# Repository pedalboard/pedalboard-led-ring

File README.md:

# An addressable RGB LED ring around foot button

| Open Source Hardware | OSHWA Certification|
|---|---|
|  |  |

Features:

- Each of the 12 LEDs on the ring can get an individual color.
- The led rings can be cascaded and addressed via a single serial line.
- Connector options: SMD Sockets (2mm, 4 Pins)
- Optional solution to drive the LED ring directly from 3.3V data pin, however the 1st LED have a bit lower intensity.

See a [live demo](https://www.youtube.com/watch?v=p5gpGeihErE) where the LED ring is used to represent the LUVS loudness value of signal.

| Top View | Bottom View  |
| -------- | ------------ |
|  |   |
|  |  |

## Generated Hardware Documentation

Interactive [KiCanvas](https://kicanvas.org/?github=https%3A%2F%2Fgithub.com%2Fpedalboard%2Fpedalboard-led-ring%2Ftree%2Fmain) viewer.

Downloadable [Assets](https://pedalboard.github.io/pedalboard-led-ring/latest) are generated with [KiBot](https://github.com/INTI-CMNB/KiBot)

## Fabrication

* [Generated iBOM](https://pedalboard.github.io/pedalboard-led-ring/latest/Assembly/pedalboard-led-ring-ibom.html)
* [Digi-Key shared list](https://www.digikey.ch/de/mylists/list/I3LZUQ0FSV)
* [PCBWay manifacturing](https://www.pcbway.com/project/shareproject/FIXME.html)

## Additional mechanical components

* Foot switch actuator: [Data Sheet](https://www.cliffuk.co.uk/products/switches/FC7125.pdf) [3D Model](https://github.com/pedalboard/pedalboard-case/blob/main/generated/actuator.stl)
* Lens: [3D Model](https://github.com/pedalboard/pedalboard-case/blob/main/generated/led-ring-washer.stl) Potential [material](https://plastics-rubber.basf.com/global/de/performance_polymers/products/ultramid.html)

## Release

The release procedure is the same as for [pedalboard-hw](https://github.com/pedalboard/pedalboard-hw#release)

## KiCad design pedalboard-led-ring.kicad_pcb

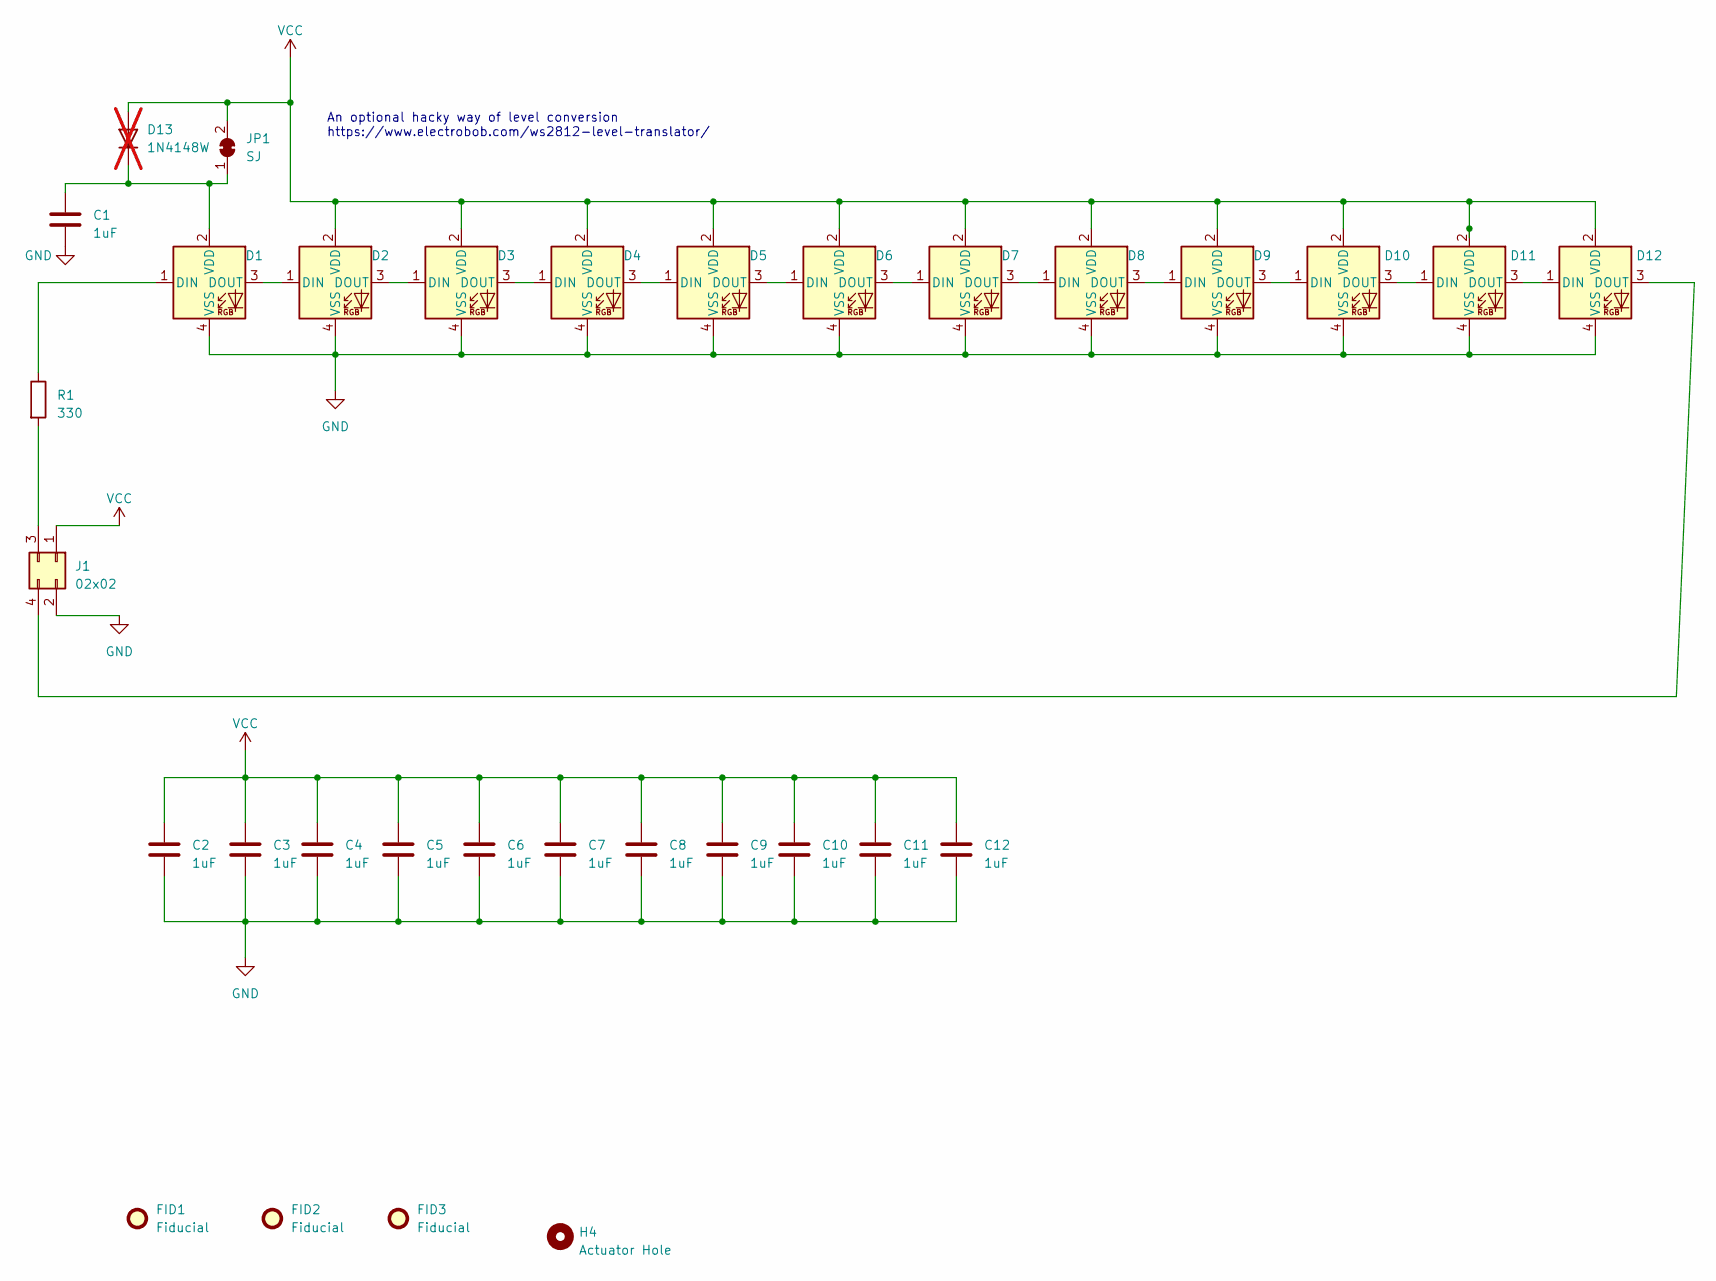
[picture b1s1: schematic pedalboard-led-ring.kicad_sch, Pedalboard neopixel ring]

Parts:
C1, C2, C3, C4, C5, C6, C7, C8, C9, C10, C11, C12: 1uF; C_0402_1005Metric
D1, D2, D3, D4, D5, D6, D7, D8, D9, D10, D11, D12: SK6812_EC15; LED_SK6812_EC15_1.5x1.5mm
D13: 1N4148W; D_SOD-923; not fitted
FID1, FID2, FID3: Fiducial; Fiducial_0.5mm_Mask1mm
H4: Actuator Hole; Actuator
J1: 02x02; PinSocket_2x02_P2.00mm_Vertical_SMD
JP1: SJ; SolderJumper-2_P1.3mm_Bridged_RoundedPad1.0x1.5mm
R1: 330; R_0402_1005Metric

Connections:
GND: C1.2, C2.2, C3.2, C4.2, C5.2, C6.2, C7.2, C8.2, C9.2, C10.2, C11.2, C12.2, D1.4 (VSS), D2.4 (VSS), D3.4 (VSS), D4.4 (VSS), D5.4 (VSS), D6.4 (VSS), D7.4 (VSS), D8.4 (VSS), D9.4 (VSS), D10.4 (VSS), D11.4 (VSS), D12.4 (VSS), J1.2
unnamed: D1.1 (DIN), R1.1
unnamed: D1.3 (DOUT), D2.1 (DIN)
unnamed: C1.1, D1.2 (VDD), D13.1 (K), JP1.1 (A)
unnamed: D2.3 (DOUT), D3.1 (DIN)
unnamed: D3.3 (DOUT), D4.1 (DIN)
unnamed: D4.3 (DOUT), D5.1 (DIN)
unnamed: D5.3 (DOUT), D6.1 (DIN)
unnamed: D6.3 (DOUT), D7.1 (DIN)
unnamed: D7.3 (DOUT), D8.1 (DIN)
unnamed: D8.3 (DOUT), D9.1 (DIN)
unnamed: D9.3 (DOUT), D10.1 (DIN)
unnamed: D10.3 (DOUT), D11.1 (DIN)
unnamed: D11.3 (DOUT), D12.1 (DIN)
unnamed: D12.3 (DOUT), J1.4
unnamed: J1.3, R1.2
VCC: C2.1, C3.1, C4.1, C5.1, C6.1, C7.1, C8.1, C9.1, C10.1, C11.1, C12.1, D2.2 (VDD), D3.2 (VDD), D4.2 (VDD), D5.2 (VDD), D6.2 (VDD), D7.2 (VDD), D8.2 (VDD), D9.2 (VDD), D10.2 (VDD), D11.2 (VDD), D12.2 (VDD), D13.2 (A), J1.1, JP1.2 (B)

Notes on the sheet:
An optional hacky way of level conversion https://www.electrobob.com/ws2812-level-translator/

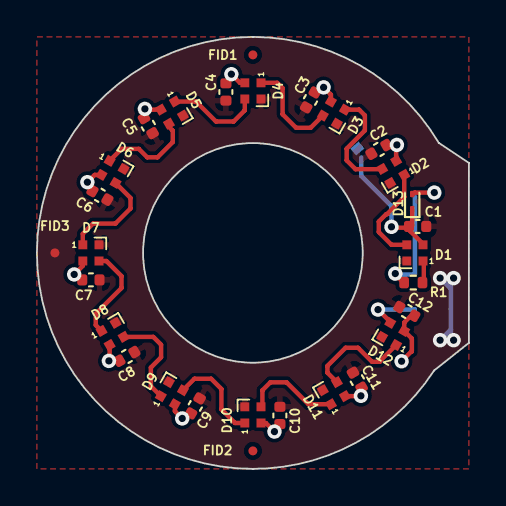
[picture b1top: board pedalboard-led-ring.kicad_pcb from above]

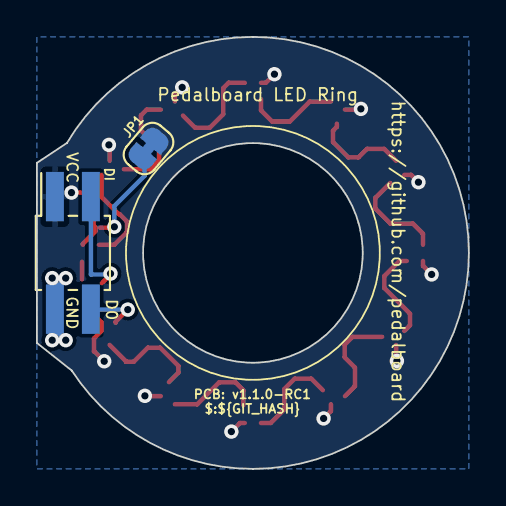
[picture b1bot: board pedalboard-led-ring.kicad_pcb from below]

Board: 2 copper layers, 24.0 x 24.0 mm, 32 parts (2 on the bottom side), 17 nets.

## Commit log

2023-05-21 First schematic with all footprints
2023-05-21 Fix ERC
2023-05-22 First routing
2023-05-22 Add some round edges
2023-05-22 Add workflow
2023-05-22 Move kibot config
2023-05-22 Improve README.md
2023-05-22 Fix secret access
2023-05-25 First version of the PSU
2023-05-25 PSU improved
2023-05-26 ERC Check fixes
2023-05-26 More 3d views
2023-05-26 Add 3d model for leds
2023-05-26 Rotate bottom view
2023-05-26 Update README.md
    add 3d views
2023-05-26 Rotate bottom view more
2023-05-26 Rotate bottom view a bit less
2023-05-26 Start to collect datasheets and parts on digikey
2023-05-26 Fix ibom link
2023-05-26 Fix connector
2023-05-26 Improve copper ground layers
2023-05-26 Improve silkscreen)
2023-05-28 Add dimensions
2023-05-28 Links to additional mechanical components
2023-05-29 Add Versioning information
2023-05-31 Update design to use neopixel
2023-06-01 Remove unused footprints from libr
2023-06-02 Improve description on silkscreen
2023-06-02 Add an input resistor as recommended by Adafruit's neopixel uberguide
2023-06-02 ERC exclkusions re-added
2023-06-02 Add 2nd connector port
2023-06-02 Add README
2023-06-02 Move vias outside of keep out area
2023-06-02 Add 3 mounting holes
2023-06-02 Silkscreen improvements
2023-06-02 Add model for actuator
2023-06-03 change 3d models
2023-06-03 Add Actuator 3d model
2023-06-03 Update README.md
    fix typo
2023-06-03 make square image size
2023-06-03 Reduce zoom level
2023-06-03 Remove blender output
2023-06-03 Reduce zoom level again
2023-06-03 Specify the parts
2023-06-03 Specify witdh of 3d images
2023-06-03 Update footprint for actuator
2023-06-03 Fix 3d Model for LEDs
2023-06-03 ignore DNP for 3d models
2023-06-03 Add led step model
2023-06-03 Improve Silkscreen
2023-06-03 change zoom level
2023-06-03 Table for 3d views
2023-06-03 Fix link to shared Digikey list
2023-06-03 3D model references in README.md
2023-06-03 Decrease size
2023-06-03 Tune zones
2023-06-03 Back to square form
2023-06-03 Move the connectors inside the smaller square
2023-06-03 Cleanup Silkscreen
2023-06-03 Top silkscreen cleanup
2023-06-03 Fix the schematic of the Neopixels
2023-06-03 Ignore ERC errors
2023-06-03 Move capacitors into the led ring radius
2023-06-03 Rerun DRC
2023-06-03 Ignore Power Pin not driven errors
2023-06-05 Move connector back to 10mm distance from center
2023-06-05 Cleanup Tracks
2023-06-20 Support 3.3V data input
2023-07-22 Fix datasheet and populate one header
2023-07-22 Improve description in README
2023-07-22 Add documentation images
2023-08-02 Update README.md
    oshw certification
2023-08-02 Add certification mark
2023-10-17 Add release procedure
2023-10-17 Link to the released docs
2023-10-17 Generate into latest
2023-10-17 Bump Version to 1.1.0-RC1
2023-10-17 Add a changelog file
2023-10-17 Simplificaitons
2023-10-17 Add fiducials for p&p
2023-10-20 Configure old version for diff
2023-10-21 Change to 0402 components
2023-10-21 Add additional Fiducial
2023-10-21 Update BOM to 0402
2023-10-22 KiCanvas link
2023-10-22 Improve explaination text
2023-10-29 Add first pnp version
2023-10-29 Place first part (LED)
2023-10-30 set all parts
2023-10-30 better panel fiducials
2023-10-30 remove placed flag
2024-01-08 Add GIT_HASH to schema and PCB
2024-01-08 Add blender output
2024-01-08 Fix GIT_HASH references
2024-01-08 Add blender view bottom
2024-01-08 Change version location on silkscreen
2024-01-10 Switch to dev version
2024-11-02 Generate bom
2026-04-14 Deploy to gh-pages branch with version picker
    - Replace cross-repo deploy with gh-pages in same repo
    - Add version picker landing page
    - Tag-triggered versioned deploy
    - Update README URLs
2026-04-14 Update CI and README for gh-pages deploy
2026-04-14 ci: use kicad7_auto_full:dev container

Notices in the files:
pedalboard-led-ring.kicad_pcb:
License: CERN Open Hardware Licence Version 2 - Permissive
